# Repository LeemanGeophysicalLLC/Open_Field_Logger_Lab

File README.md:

# Open Field Logger Lab

**Open Field Logger Lab** is a low-cost educational data logger from
[Leeman Geophysical](https://leemangeophysical.com/) for learning basic field data logging with
0-5 V analog sensors.

It is designed for students to assemble, test, and use during field measurement projects for
our [GEARS workshops](https://leemangeophysicalllc.github.io/GEARS/) and to then have a useful
tool after the course. The goal is to teach practical instrumentation concepts without turning
the logger itself into the main project.

## Purpose

This project is intended to help students learn:

- through-hole soldering
- sensor wiring
- analog voltage measurement
- calibration
- sampling rate tradeoffs
- SD card data logging
- basic field deployment practices
- the effect of real-world conditions on measurements

The logger is intentionally simple, low-cost, and easy to modify.

## What this is not

Open Field Logger Lab is **not** a precision commercial data logger.
It is not intended for safety-critical measurements, unattended long-term monitoring,
harsh environmental deployment, or calibrated scientific measurements without
additional validation.

It is a teaching platform for learning how field logging works.

## Hardware overview

Rev A is built around:

- USB-C ESP32 DevKit-style microcontroller module
- ADS1115 16-bit ADC
- four nominal 0-5 V analog single ended inputs
- microSD card logging
- battery-backed real-time clock
- 9-18 VDC input power
- 5 V sensor power output
- simple status LEDs
- optional onboard NTC temperature divider

The analog inputs are intended for simple voltage-output sensors, signal conditioning circuits,
and student-built measurement experiments.

## Student assembly philosophy

Students solder only through-hole parts. Surface-mount parts are assembled before the
workshop for time concerns. We do, however, have a surface mount soldering challenge
for those that want to try SMT!

The through-hole assembly includes parts such as connectors, fuse clips, power components,
sockets, and selected educational components.

## Repository contents

Planned contents:

```text
hardware/      KiCad design files, schematics, PCB layout, fabrication outputs, BOM
firmware/      ESP32 firmware for logging and self-test
docs/          Datasheets and other relevant files as well as assembly instructions
examples/      Example CSV files and simple analysis notebooks/scripts

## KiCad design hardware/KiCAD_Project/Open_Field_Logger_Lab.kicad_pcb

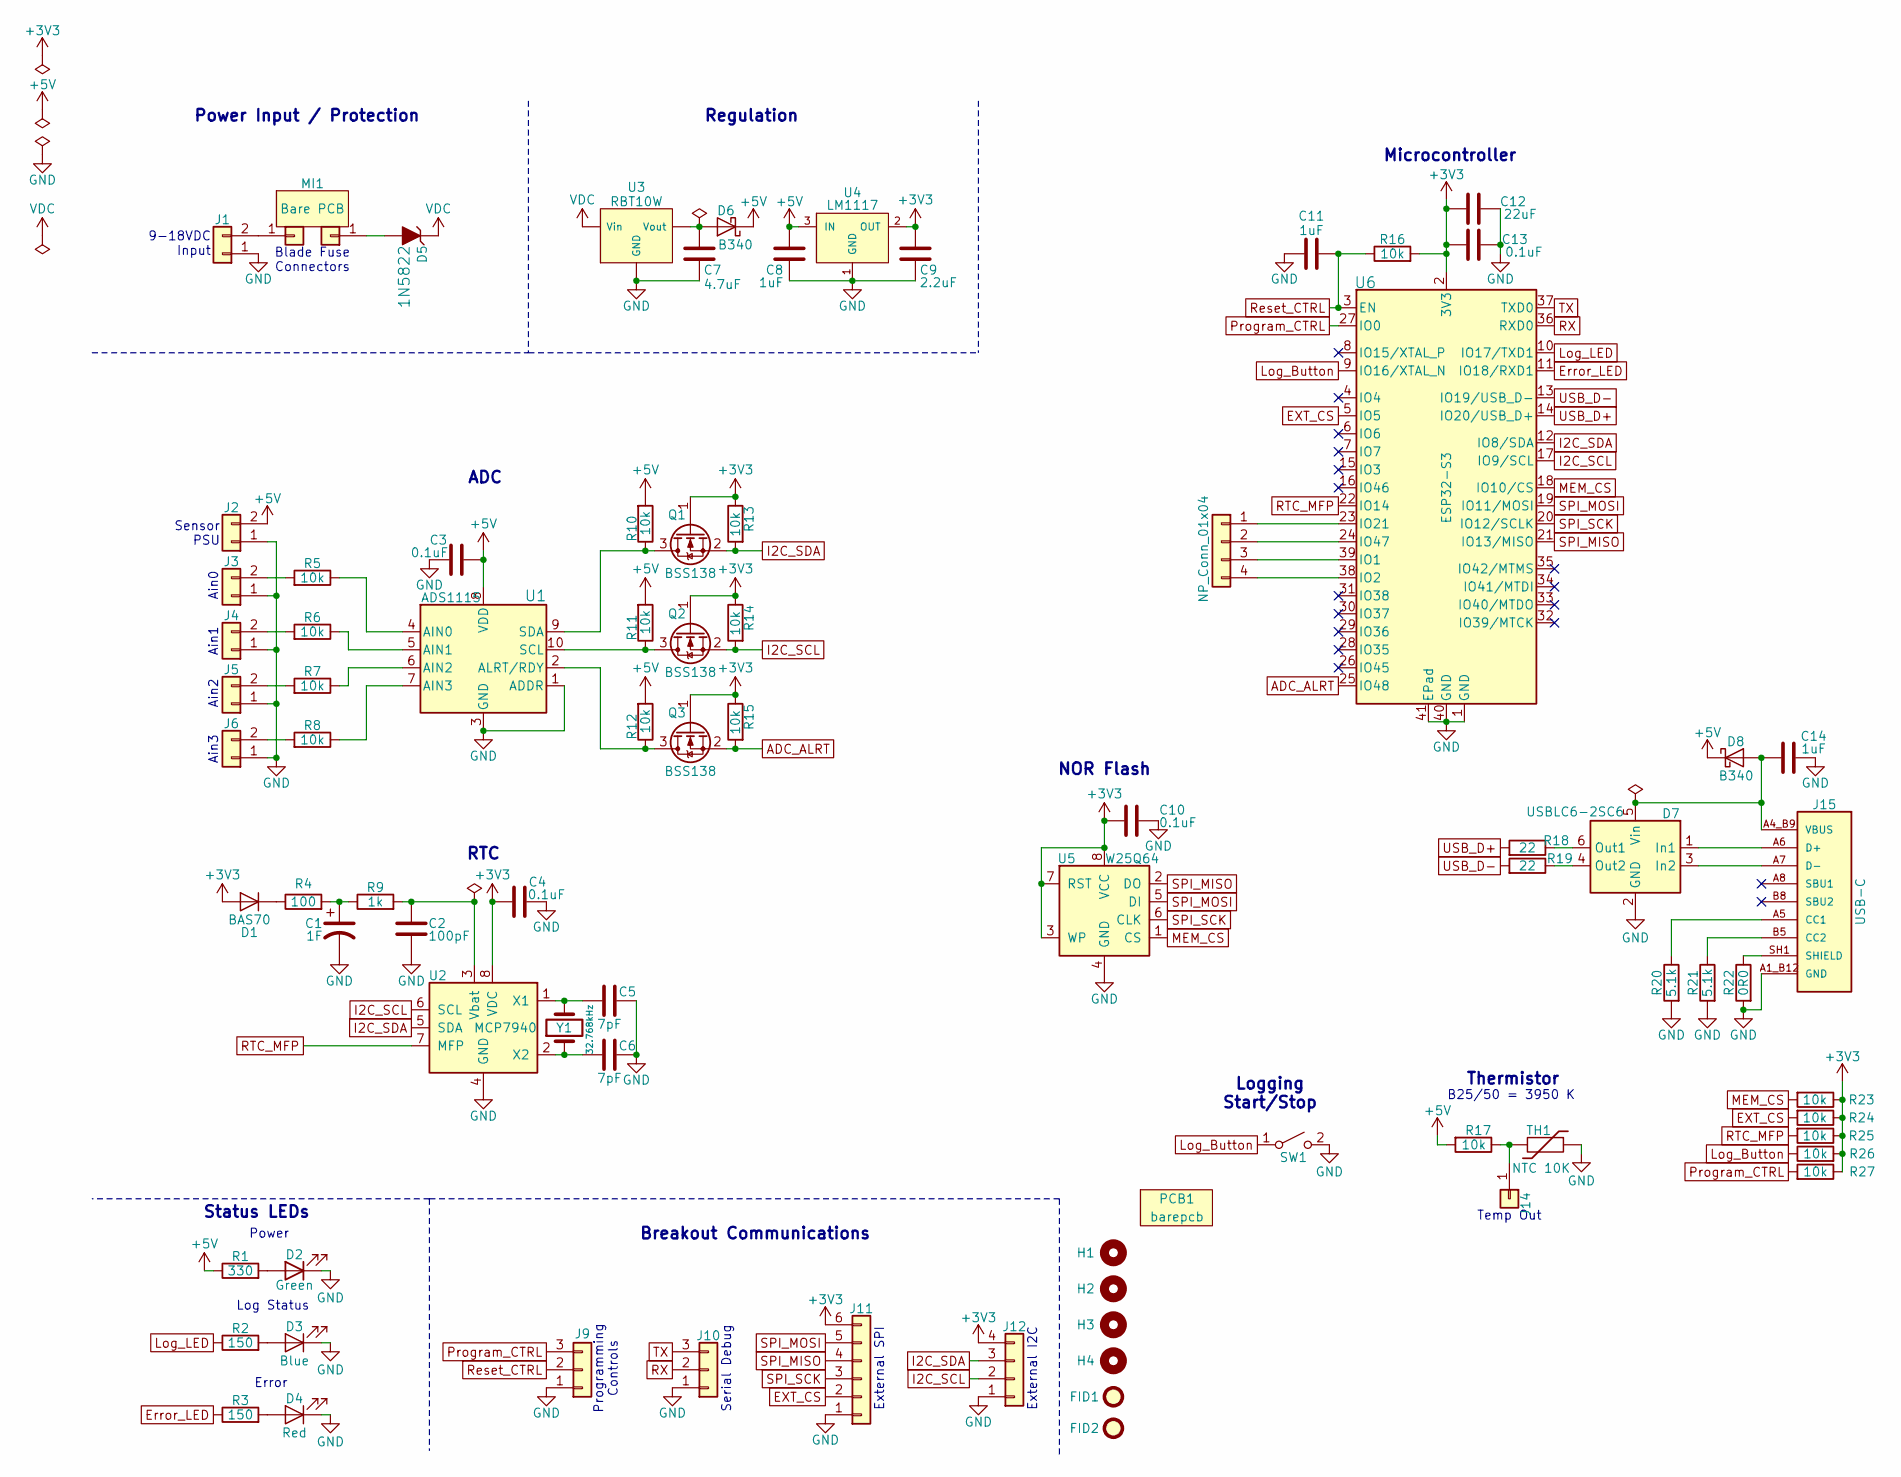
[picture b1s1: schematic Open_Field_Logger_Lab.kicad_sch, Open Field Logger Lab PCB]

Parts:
C1: 1-0001956
C2: 1-0000904
C3, C4, C10, C13: 1-0000007
C5, C6: 1-0001902
C7: 1-0000019
C8, C11, C14: 1-0000018
C9: 1-0000324
C12: 1-0000015
D1: 1-0001955
D2: 1-0001188
D3: 1-0000599
D4: 1-0000600
D5: 1-0001896
D6, D8: 1-0001977
D7: 1-0001931
FID1, FID2: Fiducial_1mm_2mm; Fiducial_1mm_Mask2mm
H1, H2, H3, H4: Imperial4; MountingHole_imperial4
J1, J2, J3, J4, J5, J6: 1-0001899
J7, J8: 1-0001894
J9, J10: NP_Conn_01x03; PinHeader_1x03_P2.54mm_Vertical
J11: NP_Conn_01x06; PinHeader_1x06_P2.54mm_Vertical
J12: NP_Conn_01x04; PinHeader_1x04_P2.54mm_Vertical
J13: AUX Input; PinHeader_1x04_P2.54mm_Vertical
J14: Conn_01x01; NP_Conn_ProtoPad
J15: 1-0001974
MI1: 1-0001895; misc_component
PCB1: barepcb
Q1, Q2, Q3: 1-0000163
R1: 1-0000369
R2, R3: 1-0000008
R4: 1-0000112
R5, R6, R7, R8, R10, R11, R12, R13, R14, R15, R16, R23, R24, R25, R26, R27: 1-0000010
R9: 1-0000013
R17: 1-0001184
R18, R19: 1-0001933
R20, R21: 1-0001859
R22: 1-0000006
SW1: 1-0000681
TH1: 1-0001897
U1: 1-0001891
U2: 1-0001892
U3: 1-0001893
U4: 1-0001973
U5: 1-0001976
U6: 1-0001927
Y1: 1-0001901

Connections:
+3V3: C4.1, C9.1, C10.1, C12.1, C13.1, D1.1 (A), J11.6, J12.4, Q1.1 (G), Q2.1 (G), Q3.1 (G), R13.1, R14.1, R15.1, R16.2, R23.1, R24.1, R25.1, R26.2, R27.1, U2.8 (VDC), U4.2 (OUT), U4.4, U5.3 (WP), U5.7 (RST), U5.8 (VCC), U6.2 (3V3)
+5V: C3.1, C8.1, D6.1 (K), D8.1 (K), J2.2, R1.1, R10.2, R11.2, R12.2, R17.2, U1.8 (VDD), U4.3 (IN)
ADC_ALRT: Q3.2 (S), R15.2, U6.25 (IO48)
EXT_CS: J11.2, R24.2, U6.5 (IO5)
Error_LED: R3.1, U6.11 (IO18/RXD1)
GND: C1.2, C2.2, C3.2, C4.2, C5.2, C6.2, C7.2, C8.2, C9.2, C10.2, C11.1, C12.2, C13.2, C14.2, D2.1 (K), D3.1 (K), D4.1 (K), D7.2 (GND), J1.1, J2.1, J3.1, J4.1, J5.1, J6.1, J9.1, J10.1, J11.1, J12.1, J15.A1_B12 (GND), J15.B1_A12 (GND), R20.2, R21.2, R22.2, SW1.2 (B), TH1.1, U1.1 (ADDR), U1.3 (GND), U2.4 (GND), U3.2 (GND), U4.1 (GND), U5.4 (GND), U6.1 (GND), U6.40 (GND), U6.41 (EPad), U6.42 (GND), U6.43 (GND), U6.44 (GND), U6.45 (GND), U6.46 (GND), U6.47 (GND), U6.48 (GND), U6.49 (GND)
I2C_SCL: J12.2, Q2.2 (S), R14.2, U2.6 (SCL), U6.17 (IO9/SCL)
I2C_SDA: J12.3, Q1.2 (S), R13.2, U2.5 (SDA), U6.12 (IO8/SDA)
Log_Button: R26.1, SW1.1 (A), U6.9 (IO16/XTAL_N)
Log_LED: R2.1, U6.10 (IO17/TXD1)
MEM_CS: R23.2, U5.1 (CS), U6.18 (IO10/CS)
unnamed: C1.1, R4.2, R9.1
unnamed: D1.3 (K), R4.1
unnamed: D2.2 (A), R1.2
unnamed: D3.2 (A), R2.2
unnamed: D4.2 (A), R3.2
unnamed: C7.1, D6.2 (A), U3.3 (Vout)
unnamed: D7.1 (In1), J15.A6 (D+), J15.B6 (D+)
unnamed: D7.3 (In2), J15.A7 (D-), J15.B7 (D-)
unnamed: D7.6 (Out1), R18.1
unnamed: D7.4 (Out2), R19.1
unnamed: J1.2, J7.1
unnamed: J3.2, R5.2
unnamed: J4.2, R6.2
unnamed: J5.2, R7.2
unnamed: J6.2, R8.2
unnamed: D5.2, J8.1
unnamed: J13.1, U6.23 (IO21)
unnamed: J13.2, U6.24 (IO47)
unnamed: J13.3, U6.39 (IO1)
unnamed: J13.4, U6.38 (IO2)
unnamed: J14.1, R17.1, TH1.2
unnamed: J15.A5 (CC1), R20.1
unnamed: J15.B5 (CC2), R21.1
unnamed: J15.SH1 (SHIELD), J15.SH2 (SHIELD), J15.SH3 (SHIELD), J15.SH4 (SHIELD), R22.1
unnamed: Q1.3 (D), R10.1, U1.9 (SDA)
unnamed: Q2.3 (D), R11.1, U1.10 (SCL)
unnamed: Q3.3 (D), R12.1, U1.2 (ALRT/RDY)
unnamed: R5.1, U1.4 (AIN0)
unnamed: R6.1, U1.5 (AIN1)
unnamed: R7.1, U1.6 (AIN2)
unnamed: R8.1, U1.7 (AIN3)
unnamed: C2.1, R9.2, U2.3 (Vbat)
unnamed: C5.1, U2.1 (X1), Y1.2
unnamed: C6.1, U2.2 (X2), Y1.1
Program_CTRL: J9.3, R27.2, U6.27 (IO0)
RTC_MFP: R25.2, U2.7 (MFP), U6.22 (IO14)
RX: J10.2, U6.36 (RXD0)
Reset_CTRL: C11.2, J9.2, R16.1, U6.3 (EN)
SPI_MISO: J11.4, U5.2 (DO), U6.21 (IO13/MISO)
SPI_MOSI: J11.5, U5.5 (DI), U6.19 (IO11/MOSI)
SPI_SCK: J11.3, U5.6 (CLK), U6.20 (IO12/SCLK)
TX: J10.3, U6.37 (TXD0)
USB_D+: R18.2, U6.14 (IO20/USB_D+)
USB_D-: R19.2, U6.13 (IO19/USB_D-)
VBUS: C14.1, D7.5 (Vin), D8.2 (A), J15.A4_B9 (VBUS), J15.B4_A9 (VBUS)
VDC: D5.1, U3.1 (Vin)

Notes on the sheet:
Temp Out
ADC
Sensor PSU
Power
Ain2
Ain0
Thermistor
B25/50 = 3950 K
RTC
Serial Debug
Ain1
External I2C
Log Status
Microcontroller
Blade Fuse Connectors
Error
Logging Start/Stop
Ain3
Power Input / Protection
Regulation
NOR Flash
Breakout Communications
Status LEDs
Programming Controls
9-18VDC Input
External SPI

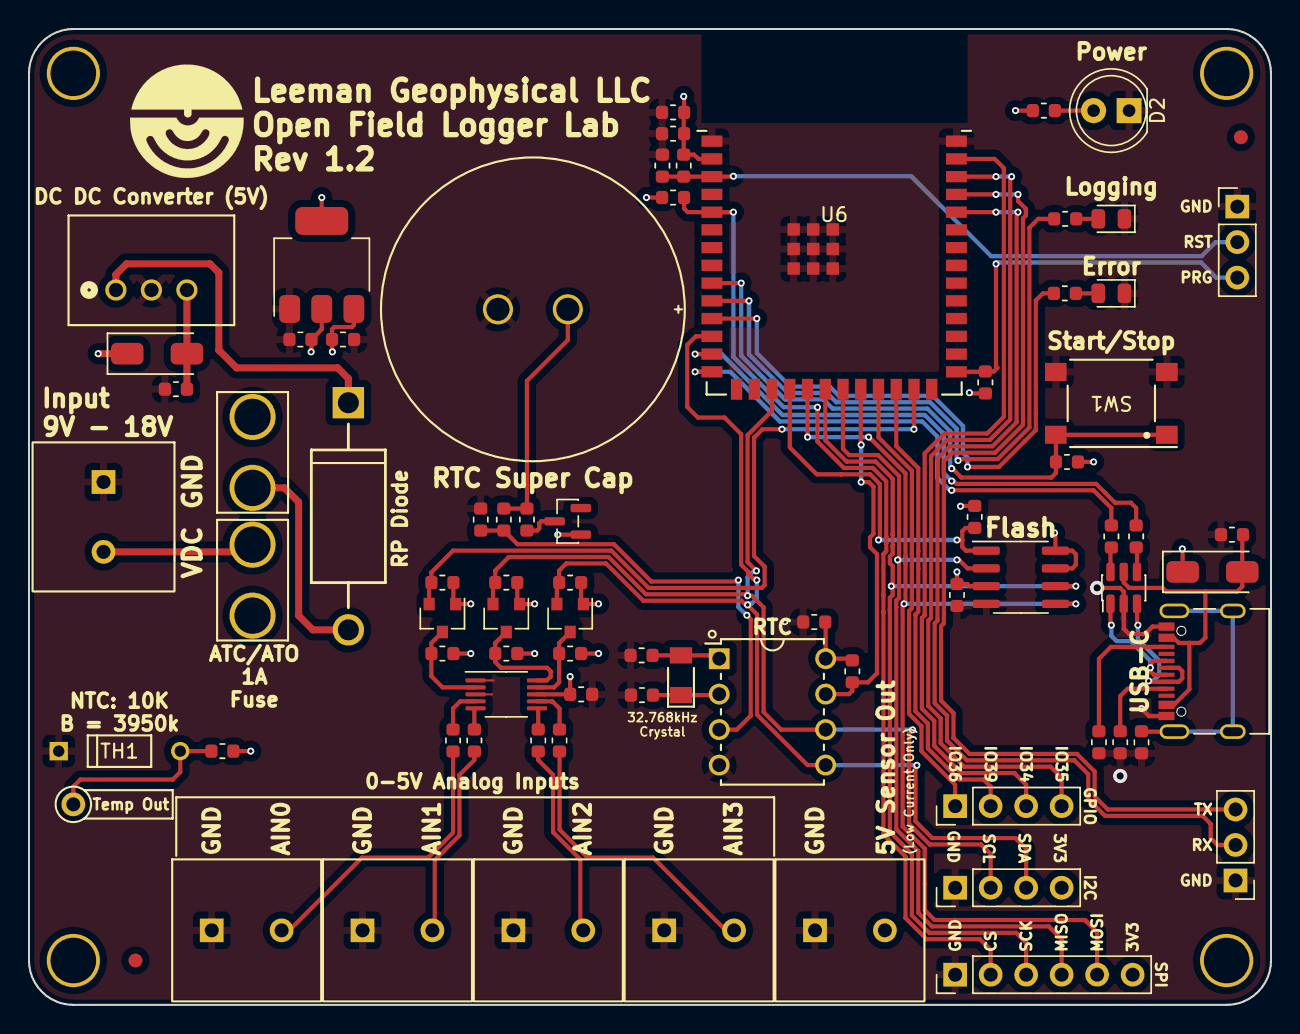
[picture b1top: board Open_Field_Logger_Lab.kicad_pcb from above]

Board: 4 copper layers, 88.9 x 69.9 mm, 84 parts (0 on the bottom side), 57 nets.

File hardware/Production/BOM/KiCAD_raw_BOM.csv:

"Reference","Value","Internal Part Number","PValue","Populated"
"BT1","1-0000863","1-0000863","CR2032","0"
"C1","1-0000019","1-0000019","4.7uF","1"
"C2","1-0000007","1-0000007","0.1uF","1"
"C3","1-0001902","1-0001902","7pF","1"
"C4","1-0001902","1-0001902","7pF","1"
"C5","1-0000007","1-0000007","0.1uF","1"
"C6","1-0000007","1-0000007","0.1uF","1"
"D1","1-0001188","1-0001188","Green","0"
"D2","1-0000599","1-0000599","Blue","1"
"D3","1-0001896","1-0001896","1N5822","0"
"D4","1-0000600","1-0000600","Red","1"
"FID1","Fiducial_1mm_2mm","0-0000000","Fiducial","0"
"FID2","Fiducial_1mm_2mm","0-0000000","Fiducial","0"
"H1","Imperial4","0-0000000","#4","0"
"H2","Imperial4","0-0000000","#4","0"
"H3","Imperial4","0-0000000","#4","0"
"H4","Imperial4","0-0000000","#4","0"
"J1","1-0001899","1-0001899","2 Pos","0"
"J2","1-0001894","1-0001894","3522","0"
"J3","1-0001894","1-0001894","3522","0"
"J4","AUX Input","0-0000000","AUX Input","0"
"J5","NP_Conn_01x03","0-0000000","NP_Conn_01x03","0"
"J6","NP_Conn_01x06","0-0000000","01x06","0"
"J7","NP_Conn_01x04","0-0000000","NP_Conn_01x04","0"
"J8","1-0000127","1-0000127","microSD","1"
"J9","Conn_01x01","","",""
"J10","1-0001899","1-0001899","2 Pos","0"
"J11","1-0001899","1-0001899","2 Pos","0"
"J12","1-0001899","1-0001899","2 Pos","0"
"J13","1-0001899","1-0001899","2 Pos","0"
"J14","1-0001899","1-0001899","2 Pos","0"
"MI1","1-0001895","1-0001895","1A","0"
"PCB1","barepcb","3-0000307","Bare PCB","1"
"Q1","1-0000163","1-0000163","BSS138","1"
"Q2","1-0000163","1-0000163","BSS138","1"
"Q3","1-0000163","1-0000163","BSS138","1"
"R1","1-0000369","1-0000369","330","1"
"R2","1-0000008","1-0000008","150","1"
"R3","1-0000010","1-0000010","10k","1"
"R4","1-0000008","1-0000008","150","1"
"R5","1-0000010","1-0000010","10k","1"
"R6","1-0000010","1-0000010","10k","1"
"R7","1-0000010","1-0000010","10k","1"
"R8","1-0000010","1-0000010","10k","1"
"R9","1-0000010","1-0000010","10k","1"
"R10","1-0000010","1-0000010","10k","1"
"R11","1-0000010","1-0000010","10k","1"
"R12","1-0000174","1-0000174","100k","1"
"R13","1-0000174","1-0000174","100k","1"
"R14","1-0001184","1-0001184","10k","1"
"R15","1-0000010","1-0000010","10k","1"
"R16","1-0000010","1-0000010","10k","1"
"R17","1-0000010","1-0000010","10k","1"
"R18","1-0000010","1-0000010","10k","1"
"SW1","1-0000681","1-0000681","Red","1"
"TH1","1-0001897","1-0001897","NTC 10K","0"
"U1","1-0001893","1-0001893","RBT10W","0"
"U2","1-0001890","1-0001890","ESP32-DevKitC","0"
"U3","1-0001892","1-0001892","MCP7940","0"
"U4","1-0001891","1-0001891","ADS1115","1"
"Y1","1-0001901","1-0001901"," 32.768kHz","1"

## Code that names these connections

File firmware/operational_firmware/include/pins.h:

#pragma once

// Open Field Logger Lab — hardware pin map.
//
// Copied from the schematic-derived table in
// firmware/board_bringup_firmware/CLAUDE.md so both firmwares agree on the
// same wiring. If the schematic ever changes, update both places.

#include <stdint.h>

// Status LEDs / button
static constexpr uint8_t PIN_ERROR_LED  = 27;  // active HIGH
static constexpr uint8_t PIN_LOG_LED    = 14;  // active HIGH
static constexpr uint8_t PIN_LOG_BUTTON = 16;  // active LOW, INPUT_PULLUP

// I2C bus (shared by the ADS1115 ADC and the MCP7940 RTC)
static constexpr uint8_t PIN_I2C_SDA = 21;
static constexpr uint8_t PIN_I2C_SCL = 22;

// SPI bus (SD card)
static constexpr uint8_t PIN_SPI_SCK  = 18;
static constexpr uint8_t PIN_SPI_MISO = 19;
static constexpr uint8_t PIN_SPI_MOSI = 23;
static constexpr uint8_t PIN_SD_CS    = 5;
static constexpr uint8_t PIN_SD_CD    = 32;  // LOW = card present

// I2C peripheral addresses
static constexpr uint8_t ADS1115_I2C_ADDR = 0x48;  // ADDR pin tied to GND
static constexpr uint8_t MCP7940_I2C_ADDR = 0x6F;

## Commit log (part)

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2026-06-15 Initial PCB Layout
2026-06-15 Updated PCB title block, Added PCB# silk
2026-06-16 Rev 1.0 production files
2026-06-29 Fixed Issues: #2 #3 #4
2026-06-30 Issue Revision: #6
